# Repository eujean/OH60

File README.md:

# OH60
Open Hardware Simple 60% Mechanical Keyboard

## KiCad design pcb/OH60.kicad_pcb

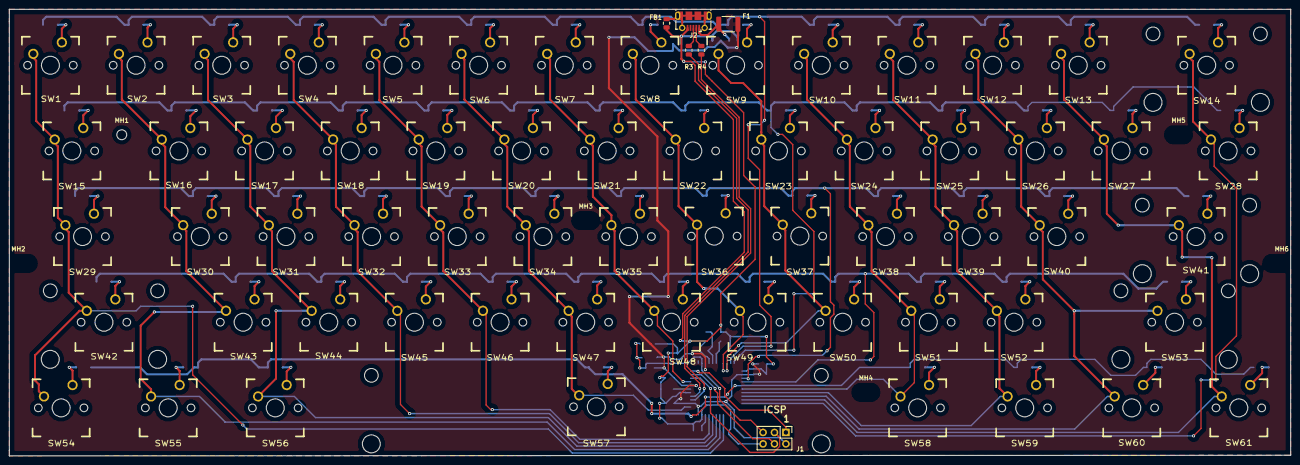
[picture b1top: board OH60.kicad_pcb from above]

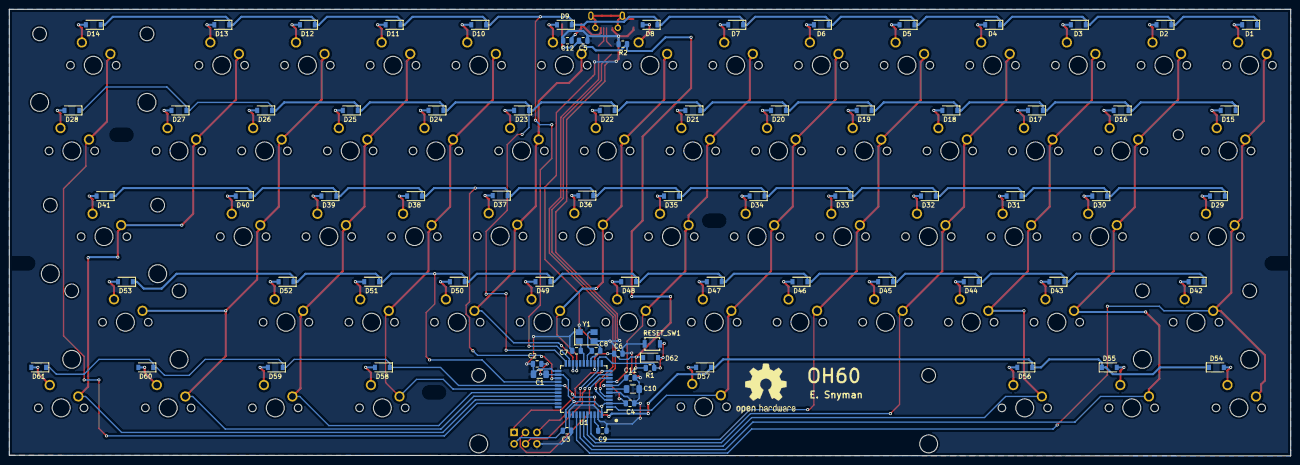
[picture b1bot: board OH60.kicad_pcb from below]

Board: 2 copper layers, 285.0 x 99.3 mm, 152 parts (79 on the bottom side), 96 nets.

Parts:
C1, C10: 1u; C_1206_3216Metric
C2, C3, C4, C5, C6, C9, C11: 100n; C_0805_2012Metric
C7, C8: 22pF; C_0805_2012Metric
C12: 22uF; C_0805_2012Metric
D1, D2, D3, D4, D5, D6, D7, D8, D9, D10, D11, D12, D13, D14, D15, D16, D17, D18, D19, D20, D21, D22, D23, D24, D25, D26, D27, D28, D29, D30, D31, D32, D33, D34, D35, D36, D37, D38, D39, D40, D41, D42, D43, D44, D45, D46, D47, D48, D49, D50, D51, D52, D53, D54, D55, D56, D57, D58, D59, D60, D61: D_ALT; D_SOD-123
D62: 1n4148; D_SOD-123
F1: MF-MSMF050-2; Fuse_1812_4532Metric
FB1: Ferrite_Bead; R_0805_2012Metric
J1: Conn_02x03_Odd_Even; PinHeader_2x03_P2.54mm_Vertical
J2: USB_B_Micro; USB_Micro-B_Molex-105017-0001
MH1, MH2, MH3, MH4, MH5, MH6: MountingHole; MountingHole_2.2mm_M2
R1, R2: 10k; R_0805_2012Metric
R3, R4: 22R; R_0805_2012Metric
RESET_SW1: SW_Push; SW_SPST_B3U-1000P
SW1, SW2, SW3, SW4, SW5, SW6, SW7, SW8, SW9, SW10, SW11, SW12, SW13, SW16, SW17, SW18, SW19, SW21, SW22, SW23, SW24, SW25, SW26, SW27, SW30, SW31, SW32, SW33, SW34, SW35, SW36, SW37, SW38, SW39, SW40, SW43, SW44, SW45, SW46, SW47, SW48, SW49, SW50, SW51, SW52: SW_SPST; CHERRY_PCB_100H
SW14: SW_SPST; CHERRY_PCB_200H
SW15, SW20, SW28: SW_SPST; CHERRY_PCB_150H
SW29: SW_SPST; CHERRY_PCB_175H
SW41, SW42: SW_SPST; CHERRY_PCB_225H
SW53: SW_SPST; CHERRY_PCB_275H
SW54, SW55, SW56, SW58, SW59, SW60, SW61: SW_SPST; CHERRY_PCB_125H
SW57: SW_SPST; CHERRY_PCB_625H
U1: ATmega32U4-AU; TQFP-44_10x10mm_P0.8mm
Y1: 16MHz; Crystal_SMD_5032-4Pin_5.0x3.2mm

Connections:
+5V: C1.1, C2.1, C3.1, C4.1, C5.1, C6.1, C11.1, D62.1, F1.1, J1.2, R1.1, R2.2, U1.2, U1.7, U1.14, U1.24, U1.34, U1.44
/matrix/COL_0: SW1.2, SW15.2, SW29.2, SW42.2, SW54.2, U1.37
/matrix/COL_1: SW2.2, SW16.2, SW30.2, SW43.2, SW55.2, U1.38
/matrix/COL_2: SW3.2, SW17.2, SW31.2, SW44.2, SW56.2, U1.39
/matrix/COL_3: SW4.2, SW18.2, SW32.2, SW45.2, U1.40
/matrix/COL_4: SW5.2, SW19.2, SW33.2, SW46.2, U1.41
/matrix/COL_5: SW6.2, SW20.2, SW34.2, SW47.2, SW57.2, U1.1
/matrix/COL_6: SW7.2, SW21.2, SW35.2, SW48.2, U1.8
/matrix/COL_7: SW8.2, SW22.2, SW36.2, SW49.2, U1.19
/matrix/COL_8: SW9.2, SW23.2, SW37.2, SW50.2, U1.20
/matrix/COL_9: SW10.2, SW24.2, SW38.2, SW51.2, SW58.2, U1.28
/matrix/COL_10: SW11.2, SW25.2, SW39.2, SW52.2, SW59.2, U1.29
/matrix/COL_11: SW12.2, SW26.2, SW40.2, SW53.2, SW60.2, U1.30
/matrix/COL_12: SW13.2, SW27.2, SW41.2, SW61.2, U1.31
/matrix/COL_13: SW14.2, SW28.2, U1.32
/matrix/ROW_0: D1.1, D2.1, D3.1, D4.1, D5.1, D6.1, D7.1, D8.1, D9.1, D10.1, D11.1, D12.1, D13.1, D14.1, U1.21
/matrix/ROW_1: D15.1, D16.1, D17.1, D18.1, D19.1, D20.1, D21.1, D22.1, D23.1, D24.1, D25.1, D26.1, D27.1, D28.1, U1.22
/matrix/ROW_2: D29.1, D30.1, D31.1, D32.1, D33.1, D34.1, D35.1, D36.1, D37.1, D38.1, D39.1, D40.1, D41.1, U1.25
/matrix/ROW_3: D42.1, D43.1, D44.1, D45.1, D46.1, D47.1, D48.1, D49.1, D50.1, D51.1, D52.1, D53.1, U1.26
/matrix/ROW_4: D54.1, D55.1, D56.1, D57.1, D58.1, D59.1, D60.1, D61.1, U1.27
/mcu/D+: R3.1, U1.4
/mcu/D-: R4.1, U1.3
/mcu/MISO: J1.1, U1.11
/mcu/MOSI: J1.4, U1.10
/mcu/PRE_D+: J2.3, R3.2
/mcu/PRE_D-: J2.2, R4.2
/mcu/RESET: D62.2, J1.5, R1.2, RESET_SW1.2, U1.13
/mcu/SCK: J1.3, U1.9
GND: C1.2, C2.2, C3.2, C4.2, C5.2, C6.2, C7.2, C8.2, C9.2, C10.2, C11.2, C12.2, FB1.2, J1.6, J2.5, R2.1, RESET_SW1.1, U1.5, U1.15, U1.23, U1.35, U1.43, Y1.2, Y1.4
unnamed: C7.1, U1.17, Y1.1
unnamed: C8.1, U1.16, Y1.3
unnamed: C9.1, U1.42
unnamed: C10.1, U1.6
unnamed: C12.1, F1.2, J2.1
unnamed: D1.2, SW1.1
unnamed: D2.2, SW2.1
unnamed: D3.2, SW3.1
unnamed: D4.2, SW4.1
unnamed: D5.2, SW5.1
unnamed: D6.2, SW6.1
unnamed: D7.2, SW7.1
unnamed: D8.2, SW8.1
unnamed: D9.2, SW9.1
unnamed: D10.2, SW10.1
unnamed: D11.2, SW11.1
unnamed: D12.2, SW12.1
unnamed: D13.2, SW13.1
unnamed: D14.2, SW14.1
unnamed: D15.2, SW15.1
unnamed: D16.2, SW16.1
unnamed: D17.2, SW17.1
unnamed: D18.2, SW18.1
unnamed: D19.2, SW19.1
unnamed: D20.2, SW20.1
unnamed: D21.2, SW21.1
unnamed: D22.2, SW22.1
unnamed: D23.2, SW23.1
unnamed: D24.2, SW24.1
unnamed: D25.2, SW25.1
unnamed: D26.2, SW26.1
unnamed: D27.2, SW27.1
unnamed: D28.2, SW28.1
unnamed: D29.2, SW29.1
unnamed: D30.2, SW30.1
unnamed: D31.2, SW31.1
unnamed: D32.2, SW32.1
unnamed: D33.2, SW33.1
unnamed: D34.2, SW34.1
unnamed: D35.2, SW35.1
unnamed: D36.2, SW36.1
unnamed: D37.2, SW37.1
unnamed: D38.2, SW38.1
unnamed: D39.2, SW39.1
unnamed: D40.2, SW40.1
unnamed: D41.2, SW41.1
unnamed: D42.2, SW42.1
unnamed: D43.2, SW43.1
unnamed: D44.2, SW44.1
unnamed: D45.2, SW45.1
unnamed: D46.2, SW46.1
unnamed: D47.2, SW47.1
unnamed: D48.2, SW48.1
unnamed: D49.2, SW49.1
unnamed: D50.2, SW50.1
unnamed: D51.2, SW51.1
unnamed: D52.2, SW52.1
unnamed: D53.2, SW53.1
unnamed: D54.2, SW54.1
unnamed: D55.2, SW55.1
unnamed: D56.2, SW56.1
unnamed: D57.2, SW57.1
unnamed: D58.2, SW58.1
unnamed: D59.2, SW59.1
unnamed: D60.2, SW60.1
unnamed: D61.2, SW61.1
unnamed: FB1.1, J2.6

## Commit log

2018-12-11 Started adding initial key matrix and doing basic layout
2018-12-11 Finished with initial layout of matrix
2018-12-13 Started adding MCU
2018-12-14 Started routing a few tracks and minor matrix adjustments
2018-12-14 Continued adding a few tracks for the matrix
2018-12-15 Continued adding some tracks around the MCU
2018-12-19 Mostly finished laying out the basic tracks
2018-12-19 Added mounting holes to the PCB
2018-12-19 Finished fixing silk-screen and zone-fills
2018-12-19 Added the missing drill file
2018-12-20 Added the required cad files for rendering and adjusted accordingly. Still no 6.25 stabilizer
2019-03-06 Added initial BOM file
2019-03-15 Updated the BOM with prices
2019-03-18 Updated 10k resistor for an in-stock variant
2019-03-26 Updated BOM with borders
2019-03-26 Added switch plate files with dimensions
2019-04-08 Added the outstanding layers for the sandwich case
